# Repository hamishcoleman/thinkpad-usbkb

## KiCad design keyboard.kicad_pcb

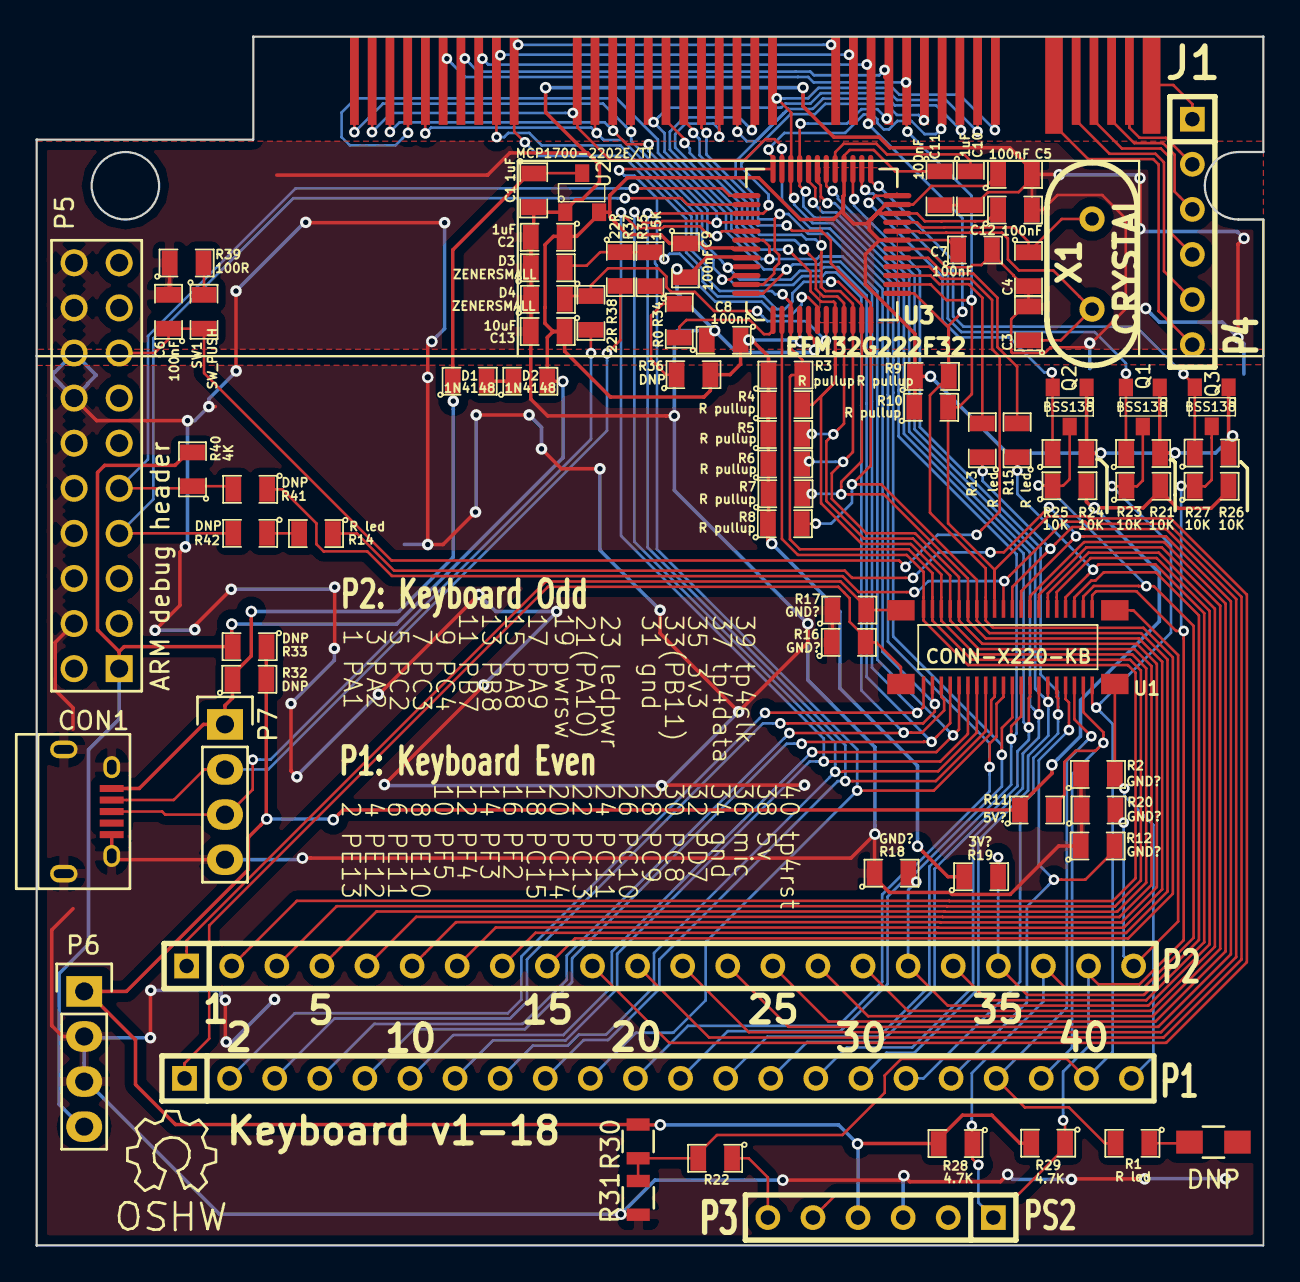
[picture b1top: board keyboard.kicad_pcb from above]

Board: 2 copper layers, 69.1 x 68.1 mm, 76 parts (0 on the bottom side), 75 nets.

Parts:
C1, C2, C10: 1uF; SM0805
C3, C4: C; SM0805
C5, C6, C7, C8, C9, C11, C12: 100nF; SM0805
C13: 10uF; SM0805
CON1: USB-MICRO-B; USB_Micro-B
D1, D2: 1N4148; SM0805
D3, D4: ZENERSMALL; SM0805
J1: CONN-PALM-FOLD-KB; conn-palm-fold-kb
P1: P1: Keyboard Even; SIL-26
P2: P2: Keyboard Odd; SIL-26
P3: PS2; SIL-6
P4: Palm Serial; SIL-6
P5: ARM debug header; pin_array_10x2
P6: Power; Pin_Header_Straight_1x04
P7: USB_H; Pin_Header_Straight_1x04
Q1, Q2, Q3: BSS138; SOT23
R1, R13, R14, R15: R led; SM0805
R2, R12, R16, R17, R18, R20: GND?; SM0805
R3, R4, R5, R6, R7, R8, R9, R10: R pullup; SM0805
R11: 5V?; SM0805
R19: 3V?; SM0805
R21, R23, R24, R25, R26, R27: 10K; SM0805
R22, R34: R0; SM0805
R28, R29: 4.7K; SM0805
R30, R31: DNP; R_0805
R32, R33, R36, R41, R42: DNP; SM0805
R35: 1.5K; SM0805
R37, R38: 22R; SM0805
R39: 100R; SM0805
R40: 4K; SM0805
SW1: SW_PUSH; SM0805
U1: CONN-X220-KB; AA01B-S040VA1
U2: MCP1700-2202E/TT; SOT23
U3: EFM32G222F32; EFM32_TQFP48
X1: CRYSTAL; HC-49V

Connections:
+3V3: C2.1, C5.1, C7.1, C8.1, C9.1, C11.1, C12.1, C13.1, D2.2, P5.1, P6.4, Q1.1, Q2.1, Q3.1, R3.1, R4.1, R5.1, R6.1, R7.1, R8.1, R9.1, R10.1, R19.1, R21.2, R24.2, R26.2, R33.2, R36.2, R40.2, U2.2, U3.4, U3.19, U3.22, U3.23, U3.28, U3.43
+5V: P3.4, P6.1, R11.1, R23.2, R25.2, R27.2, R28.2, R29.2, R30.2, R32.2, R33.1
/keyboard-efm32/#RESET: C6.1, P5.15, SW1.2, U3.16
/keyboard-efm32/SWCLK: P5.9, R40.1, R41.2, U3.37
/keyboard-efm32/SWDIO: P5.7, R42.2, U3.38
/keyboard-efm32/USB_DM: D3.2, R35.2, R37.1, U3.6
/keyboard-efm32/USB_DP: D4.2, R38.1, U3.7
/keyboard-efm32/USB_SENSE: R34.1, U3.1
/keyboard-efm32/ps2_clk: Q3.2, R26.1, U3.25
/keyboard-efm32/ps2_data: Q2.2, R24.1, U3.24
/keyboard-efm32/ps2_reset: Q1.2, R21.1, U3.26
/keyboard-power/VBUS: C1.1, CON1.1, D1.1, P7.1, R32.1, U2.3
GND: C1.2, C2.2, C3.2, C4.2, C5.2, C6.2, C7.2, C8.2, C9.2, C10.2, C11.2, C12.2, C13.2, CON1.5, CON1.6, CON1.7, CON1.8, CON1.9, D3.1, D4.1, P3.3, P5.4, P5.6, P5.8, P5.10, P5.12, P5.14, P5.16, P5.18, P5.20, P6.2, P6.3, P7.4, R2.1, R12.1, R16.1, R17.1, R18.1, R20.1, R31.1, R39.1, U2.1, U3.5, U3.18, U3.44
unnamed: C3.1, U3.20, X1.1
unnamed: C4.1, U3.21, X1.2
unnamed: C10.1, U3.29
unnamed: CON1.2, P7.2, R37.2
unnamed: CON1.3, P7.3, R38.2
unnamed: D1.2, D2.1
unnamed: J1.1, P4.1
unnamed: J1.2, P4.2
unnamed: J1.3, P4.3
unnamed: J1.4, P4.4
unnamed: J1.5, P4.5
unnamed: J1.6, P4.6
unnamed: P1.1, R16.2, U1.42
unnamed: P1.18, R12.2, U1.34
unnamed: P1.19, R1.2, U1.36
unnamed: P1.20, R11.2, U1.38
unnamed: P1.22, R2.2, U1.44
unnamed: P2.1, R17.2, U1.41
unnamed: P2.12, R13.1, U1.21
unnamed: P2.13, R14.1, U1.23
unnamed: P2.17, R18.2, U1.31
unnamed: P2.18, R15.1, U1.33
unnamed: P2.19, R19.2, U1.35
unnamed: P2.22, R20.2, U1.43
unnamed: P3.6, R22.1
unnamed: R34.2, R35.1, R36.1
unnamed: R39.2, SW1.1
col1: J1.7, J1.17, P1.12, U1.22, U3.34
col2: J1.10, P1.10, U1.18, U3.36
col3: J1.35, P1.8, U1.14, U3.40
col4: J1.18, P1.6, U1.10, U3.42
col5: J1.8, J1.24, P1.2, U1.2, U3.48
col6: J1.9, J1.19, P1.3, U1.4, U3.47
col7: J1.25, J1.38, P1.5, U1.8, U3.45
col8: J1.26, J1.36, P1.7, U1.12, U3.41
col9: J1.27, J1.34, P1.4, U1.6, U3.46
col10: J1.28, J1.37, P1.11, U1.20, U3.35
col11: J1.11, P1.9, U1.16, U3.39
col12: J1.13, J1.32, P1.13, U1.24, U3.33
col13: P1.15, U1.28, U3.31
col14: P1.17, U1.32, U3.27
col15: P1.14, U1.26, U3.32
col16: P1.16, U1.30, U3.30
hotkey: P2.2, U1.1, U3.2
kbdid0: P2.14, U1.25
kbdid1: P2.15, U1.27
kbdid2: P2.16, U1.29
led_mute: R15.2, U3.17
ledcpslock: R13.2, U3.15
ledpwr: R14.2, R42.1
pwrswitch: P2.11, R41.1, U1.19
row1: J1.20, P2.4, R4.2, U1.5, U3.8
row2: J1.21, P2.8, R8.2, U1.13, U3.12
row3: J1.22, P2.6, R6.2, U1.9, U3.10
row4: J1.23, P2.5, R5.2, U1.7, U3.9
row5: J1.16, J1.29, P2.7, R7.2, U1.11, U3.11
row6: J1.15, J1.30, P2.3, R3.2, U1.3, U3.3
row7: J1.14, J1.31, P2.9, R9.2, U1.15, U3.13
row8: J1.12, J1.33, P2.10, R10.2, U1.17, U3.14
tp4_clk: P2.21, P3.5, Q3.3, R27.1, R29.1, U1.39
tp4_reset: P1.21, Q1.3, R22.2, R23.1, R30.1, R31.2, U1.40
tp4data: P2.20, P3.1, Q2.3, R25.1, R28.1, U1.37

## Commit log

2015-03-03 Add pre-git notes to project
2015-03-04 Add some details for an old palm foldable keyboard
2015-03-19 Add some more links
2015-03-19 Add a footprint for the keyboard connector
2015-03-20 Add schematic component for keyboard
2015-03-20 Update connector to use correct footprint
2015-03-20 Add a connector for the palm keyboard
2015-03-20 Add keyboard project, with initial schematic and pcb layout
2015-03-20 Add the start of a footprint for the palm folding keyboard
2015-03-20 Update keyboard
2015-03-20 Start work on PCB - note, using newer kicad
2015-03-20 Slight correction of the palm footprint
2015-03-20 Add two dimension squares to the PCB
2015-03-20 Add an option jumper for the reset line going to the PS2 connector
2015-03-20 Add another jumper option and update pcb
2015-03-20 Move thinkpad keyboard connector to a sub sheet
2015-03-21 Split into more sheets, adding ps2mouse and power
2015-03-21 Add USB port
2015-03-21 Add energymicro component library from https://github.com/hairykiwi/csv2kicad.git
2015-03-21 Add footprints from https://github.com/EnergyMicro/HackaGecko/blob/master/Kicad_3D/Footprints/EnergyMicro.mod
2015-03-21 Add new sheet for microcontroller
2015-03-22 Join microcontroller to all the peripherals
2015-03-22 Correct pin directions for ldo
2015-03-22 assign part numbers, also document two keyboard connections that we had no gpio for
2015-03-22 Assign footprints
2015-03-22 When we no longer need SWD, we can use two more keyboard io lines
2015-03-22 Import all components into PCB
2015-03-22 Give some components better labels, start playing around with initial part placement
2015-03-22 Overlay the palm pcb footprint and start jamming parts into that shape
2015-03-22 Attempt to interpret http://tinyurl.com/hvpcbfaq as kicad config
2015-03-22 First pass at joining up the duplicated palm connections
2015-03-23 Route most of the palm board, ensuring that there was also enough escape for the rest of the board
2015-03-25 BUG: diode droppers end up at 3.3v, not 5v
2015-03-27 Fully routed board, done with new kicad 5533
2015-03-27 Add a gerbv project
2015-03-27 Tidy up silkscreen and one gnd plane misplaced via
2015-03-27 Adjust palm connector silkscreen to really not show up
2015-03-27 Add open source logo
2015-03-27 Fix nets crossing - GND with reset
2015-03-27 Ran DRC and it wanted to save the change - cannot see any change
2015-03-29 Add micro usb footprint from dangerous prototypes - https://dangerous-prototypes-open-hardware.googlecode.com/svn/trunk/Kicad_Part_Library
2015-03-30 Update USB footprint, clean up more minor PCB warts
2015-03-31 Add pin some labels to silkscreen
2015-03-31 Bump version number on board
2015-03-31 Fix extra traces under microsd
2015-03-31 Imported board_redraw_dimensions.dxf and adjusted the Palm footprint to match. Note: it still needs fixing in module
2015-03-31 Bump version number on silkscreen
2015-03-31 Do DRC and reflow fill
2015-03-31 Clean up silkscreen cheat sheet, mostly moving breakout description
2015-04-01 Increase size of x220 pad sizes
2015-04-01 Add gerber outputs into ignored list
2015-04-01 Add a project URL
2015-05-12 Add the svg intermediate files to the ignore list
2015-05-12 Start generating a solder stencil output, and update the edge connector to not need paste
2015-06-07 Update some of the key layout after buzzing a real keyboard
2015-06-07 Update parts spreadsheet with some quick re-quotes on the EFM32 cpu
2015-06-07 Add a makefile with some simple output rendering targets
2015-06-07 CLEANUP: some old project file updates
2015-06-07 Add a make target for creating a whole-project zip archive
2016-04-18 Add some minor notes to the bios details doc
2016-04-18 Add more notes for how to flash the EC and what to change
2016-04-18 Add details of next Fn key table and update instructions with same
2016-04-19 Update scancodes with numlock, note workaround for Fn+F2
2016-07-26 Remove table that is now in the thinkpad-ec repo
2017-01-26 Add note with guess of what the modifier byte does
2017-01-26 Add keyboard pinout notes
2017-01-26 Add some basic SWD programming information
2017-01-26 Rename outputs with better name
2018-06-06 Make it clear which licence I have always considered this under
